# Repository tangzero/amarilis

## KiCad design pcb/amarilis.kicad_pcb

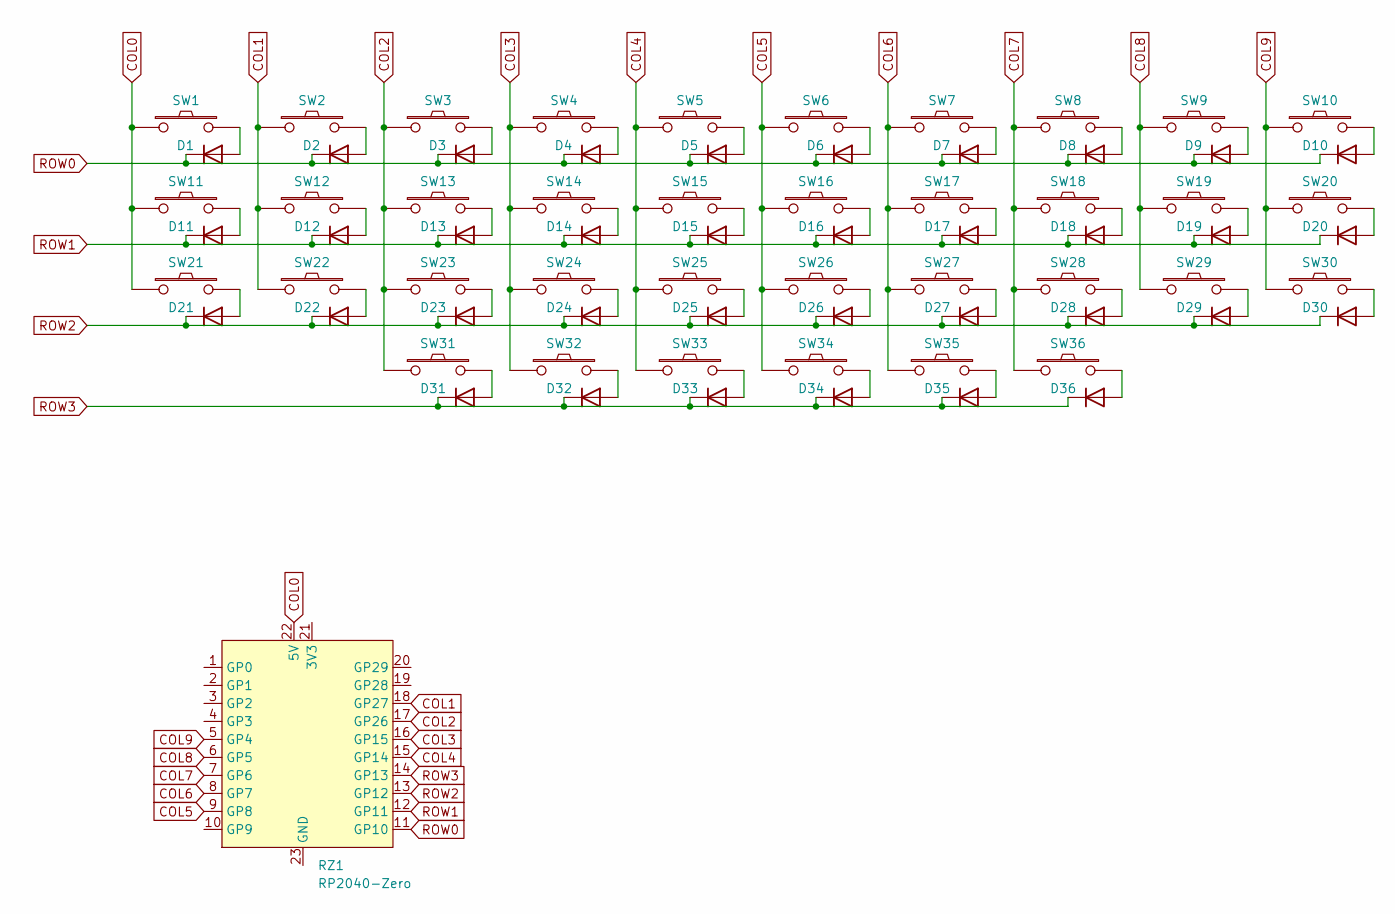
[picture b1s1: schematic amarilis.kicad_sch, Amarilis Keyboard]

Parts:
D1, D2, D3, D4, D5, D6, D7, D8, D9, D10, D11, D12, D13, D14, D15, D16, D17, D18, D19, D20, D21, D22, D23, D24, D25, D26, D27, D28, D29, D30, D31, D32, D33, D34, D35, D36: 1N4148; D3_TH
RZ1: RP2040-Zero
SW1, SW2, SW3, SW4, SW5, SW6, SW7, SW8, SW9, SW10, SW11, SW12, SW13, SW14, SW15, SW16, SW17, SW18, SW19, SW20, SW21, SW22, SW23, SW24, SW25, SW26, SW27, SW28, SW29, SW30, SW31, SW32, SW33, SW34, SW35, SW36: SW_PUSH; CherryMX_1u

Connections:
COL0: RZ1.22 (5V), SW1.1, SW11.1, SW21.1
COL1: RZ1.18 (GP27), SW2.1, SW12.1, SW22.1
COL2: RZ1.17 (GP26), SW3.1, SW13.1, SW23.1, SW31.1
COL3: RZ1.16 (GP15), SW4.1, SW14.1, SW24.1, SW32.1
COL4: RZ1.15 (GP14), SW5.1, SW15.1, SW25.1, SW33.1
COL5: RZ1.9 (GP8), SW6.1, SW16.1, SW26.1, SW34.1
COL6: RZ1.8 (GP7), SW7.1, SW17.1, SW27.1, SW35.1
COL7: RZ1.7 (GP6), SW8.1, SW18.1, SW28.1, SW36.1
COL8: RZ1.6 (GP5), SW9.1, SW19.1, SW29.1
COL9: RZ1.5 (GP4), SW10.1, SW20.1, SW30.1
unnamed: D1.2 (A), SW1.2
unnamed: D2.2 (A), SW2.2
unnamed: D3.2 (A), SW3.2
unnamed: D4.2 (A), SW4.2
unnamed: D5.2 (A), SW5.2
unnamed: D6.2 (A), SW6.2
unnamed: D7.2 (A), SW7.2
unnamed: D8.2 (A), SW8.2
unnamed: D9.2 (A), SW9.2
unnamed: D10.2 (A), SW10.2
unnamed: D11.2 (A), SW11.2
unnamed: D12.2 (A), SW12.2
unnamed: D13.2 (A), SW13.2
unnamed: D14.2 (A), SW14.2
unnamed: D15.2 (A), SW15.2
unnamed: D16.2 (A), SW16.2
unnamed: D17.2 (A), SW17.2
unnamed: D18.2 (A), SW18.2
unnamed: D19.2 (A), SW19.2
unnamed: D20.2 (A), SW20.2
unnamed: D21.2 (A), SW21.2
unnamed: D22.2 (A), SW22.2
unnamed: D23.2 (A), SW23.2
unnamed: D24.2 (A), SW24.2
unnamed: D25.2 (A), SW25.2
unnamed: D26.2 (A), SW26.2
unnamed: D27.2 (A), SW27.2
unnamed: D28.2 (A), SW28.2
unnamed: D29.2 (A), SW29.2
unnamed: D30.2 (A), SW30.2
unnamed: D31.2 (A), SW31.2
unnamed: D32.2 (A), SW32.2
unnamed: D33.2 (A), SW33.2
unnamed: D34.2 (A), SW34.2
unnamed: D35.2 (A), SW35.2
unnamed: D36.2 (A), SW36.2
ROW0: D1.1 (K), D2.1 (K), D3.1 (K), D4.1 (K), D5.1 (K), D6.1 (K), D7.1 (K), D8.1 (K), D9.1 (K), D10.1 (K), RZ1.11 (GP10)
ROW1: D11.1 (K), D12.1 (K), D13.1 (K), D14.1 (K), D15.1 (K), D16.1 (K), D17.1 (K), D18.1 (K), D19.1 (K), D20.1 (K), RZ1.12 (GP11)
ROW2: D21.1 (K), D22.1 (K), D23.1 (K), D24.1 (K), D25.1 (K), D26.1 (K), D27.1 (K), D28.1 (K), D29.1 (K), D30.1 (K), RZ1.13 (GP12)
ROW3: D31.1 (K), D32.1 (K), D33.1 (K), D34.1 (K), D35.1 (K), D36.1 (K), RZ1.14 (GP13)

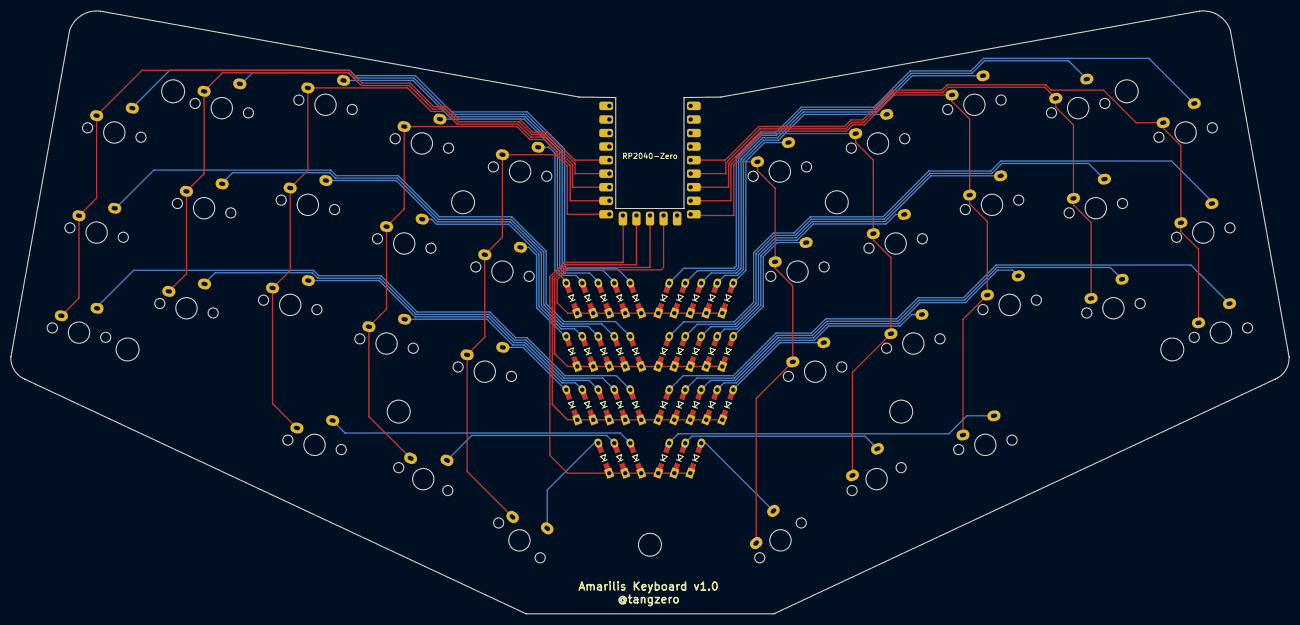
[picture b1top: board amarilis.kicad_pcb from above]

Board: 2 copper layers, 239.7 x 113.0 mm, 82 parts (0 on the bottom side), 50 nets.

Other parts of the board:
Ref**: Val**; spacer_m2
Ref**#2, Ref**#3, Ref**#4, Ref**#5, Ref**#6, Ref**#7, Ref**#8, Ref**#9: Val**; spacer_m2

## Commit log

2023-03-17 schematics done
2023-03-17 starting the PCB
2023-03-18 PCB ready!
2023-03-18 mounting holes + some traces adjustments
2023-03-18 top and bottom plates
2023-03-20 gerber files
2023-03-20 Miryoku based firmware
2023-03-20 remove unnecessary code
